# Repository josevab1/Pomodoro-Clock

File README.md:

# Pomodoro-Clock
An Embedded Project of a customizable pomodoro clock using servo's to denote Work, Rest, Edit and Cycle Completed through Arduino. Using Platform.IO via VSCode.

## To Do
* [] Optimize Code (IMPORTANT)
  *   [] Helper Library 
  *   [] Button Library
  *   [] Display Library (Maybe have specific lcd screen functions here to then use as display)
  *   [] Basic Servo Library made via PWM

* [] Add "LOCKED IN" Button, continous cycle no breaks. Make have it as a switch... Prolly more funnier using a switch,
  
* [] Plan via Perfboard
* [] CAD case
* [] Solder connections
* [] 3D Print Case

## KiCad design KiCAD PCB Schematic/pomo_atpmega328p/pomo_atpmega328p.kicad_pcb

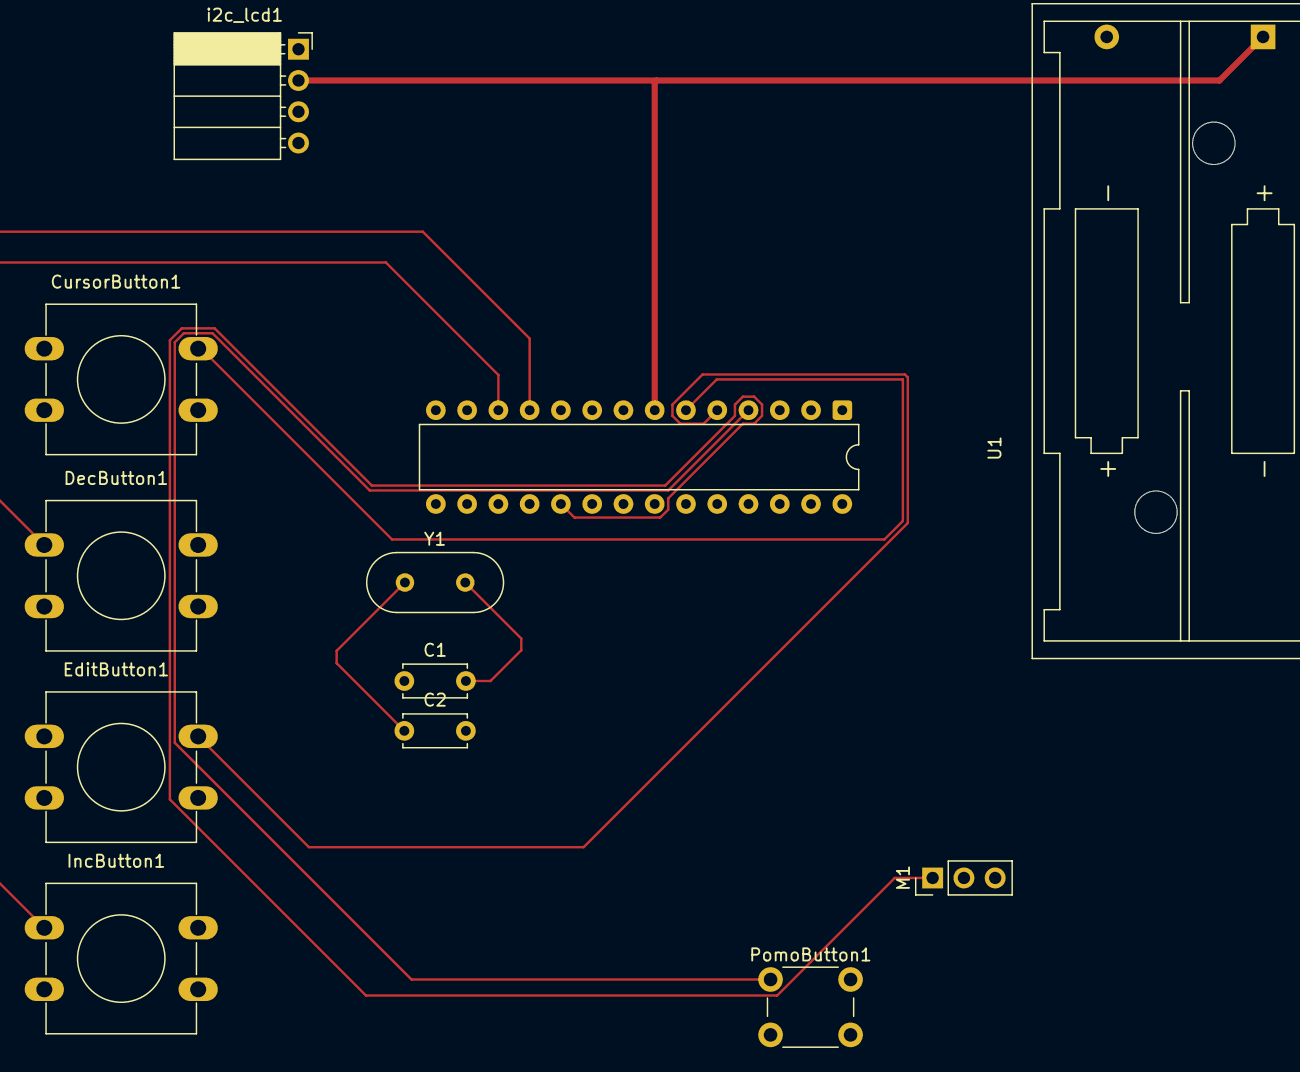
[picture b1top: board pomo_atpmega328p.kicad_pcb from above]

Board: 2 copper layers, 12 parts (0 on the bottom side), 12 nets.

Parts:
BT1: Battery; BatteryHolder_Keystone_2468_2xAAA
C1, C2: 20 pF; C_Disc_D5.0mm_W2.5mm_P5.00mm
CursorButton1: SW_MEC_5E; SW_PUSH-12mm
DecButton1: SW_MEC_5E; SW_PUSH-12mm
EditButton1: SW_MEC_5E; SW_PUSH-12mm
IncButton1: SW_MEC_5E; SW_PUSH-12mm
M1: Motor_Servo; PinHeader_1x03_P2.54mm_Vertical
PomoButton1: SW_MEC_5E; SW_PUSH_6mm
U1: ATmega328-P; DIP-28_W7.62mm
Y1: 16 MHz; Crystal_HC18-U_Vertical
i2c_lcd1: i2c_lcd_screen; PinSocket_1x04_P2.54mm_Horizontal

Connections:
+5V: BT1.1 (+), M1.2 (+), U1.7 (VCC), i2c_lcd1.2 (VDD)
GND: BT1.2 (-), C1.1, C2.2, M1.3 (-), U1.8 (GND), U1.22 (GND), i2c_lcd1.1 (VSS)
unnamed: M1.1 (PWM), U1.19 (PB5)
unnamed: U1.27 (PC4), i2c_lcd1.3 (SDA)
unnamed: U1.28 (PC5), i2c_lcd1.4 (SCK)
unnamed: PomoButton1.1 (1_1), U1.4 (PD2)
unnamed: EditButton1.1 (1_1), U1.5 (PD3)
unnamed: CursorButton1.1 (1_1), U1.6 (PD4)
unnamed: IncButton1.1 (1_1), U1.11 (PD5)
unnamed: DecButton1.1 (1_1), U1.12 (PD6)
unnamed: C1.2, U1.9 (XTAL1/PB6), Y1.2
unnamed: C2.1, U1.10 (XTAL2/PB7), Y1.1

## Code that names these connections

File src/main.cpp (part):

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Servo servo;

// For Pomodoro Mode
const uint8_t Pomodoro_Button = 2; // PD2 
// For Edit Mode
const uint8_t Edit_Button = 3; // PD3
const uint8_t Cursor_Button = 4; // PD4
const uint8_t Inc_Button = 5; // PD5
const uint8_t Dec_Button = 6; // PD6
// For Lock in Mode
// const uint8_t Lock_In_Button = 7; 

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
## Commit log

2026-01-12 Added OG code.
    Need to optimize code. Create helper library, button library, display library for the redundant codes.
    Start migration to using the I2C LCD screen.
    [MAYBE] Possibly use pwm for servo make it own library, have only necessary i2c lcd functions.
2026-01-19 LCD I2C
2026-01-19 i2c implemented. ooping why not.
2026-02-20 Fixed Bug, where when work mode done, and edit to have a work to have value freezes. By simply forcing users to never do that in interface. lol.
2026-02-23 Better Variable readability. Must put Long Rest and Lock-in modes in a later iteration. I yearn to solder and make something.
2026-03-03 Added PCB Schematic, still needs connections to be fixed.
2026-06-16 Possible atpmega328p alternative
2026-06-21 Redone ATPmega328p Schematic, need traces properly placed and schematic consider having decoup caps
